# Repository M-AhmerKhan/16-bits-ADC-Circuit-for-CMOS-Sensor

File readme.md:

# Analog-Digital conversion circuit with an interface to a FPGA development board for an X-ray detector module of a 3D breast CT prototype

## Project Overview
This project focuses on the design and development of an ADC electronic circuit for a CMOS sensor coupled with CsI:Tl scintillating crystals to detects X-rays. The circuit samples analog pixels data from the sensor, crucial for analyzing beam geometry and sensor-scintillator response. An FPGA interfaces with the circuit to process the digital data from three sensor channels and store it on a host computer for image processing and analysis.

## Features
- 16-bits ADC circuit for 3 channel CMOS sensor.
- Serial Peripheral Interface (SPI)
- Designed voltage level shifter for interfacing +3.3V Analog front end LM98725 with a +5V CMOS sensor.
- Implemented voltage clamping circuit.
- Interfacing ADC with FPGA (NI sbRIO-9651) via LabVIEW.
- PCB layout and design using EAGLE

## Tools and Technologies

- **EAGLE** for schematic capture and PCB layout
- **LabVIEW** to acquires the digital data from the ADC in a sequence, converts this data into integer values and save the complete pixels data in a text file on the computer from each sensor channel.
- **Arduino** for SPI
- **Oscilloscope** for signal testing.
- **MATLAB** for anylyzing sesor data.

## Circuit Schematic
Here is the circuit schematic designed in EAGLE:

## PCB Layout
The PCB layout was created using EAGLE. Below is a preview of the PCB design:

## Designed PCB
Final designed PCB:

## Interfacing with FPGA

The 16 bits digital data from the ADC is arranged in a particular sequence such that it gives a single pixel value from each three channels of CMOS sensor. Two  LabVIEW programs (VI) source code are written and complied, one on the FPGA also called “target” to collects the sensor digital data and the other on the computer system referred as “host”. This data is received and saved to the host memory in the same order by implementing a FIFO method (First In First Out) that organize and prioritize the data with the time.

Communication and data flow between host computer and FPGA:

## Contact
For any questions, feel free to contact me at: [m.ahmerkhan@outlook.de](mailto:m.ahmerkhan@outlook.de).

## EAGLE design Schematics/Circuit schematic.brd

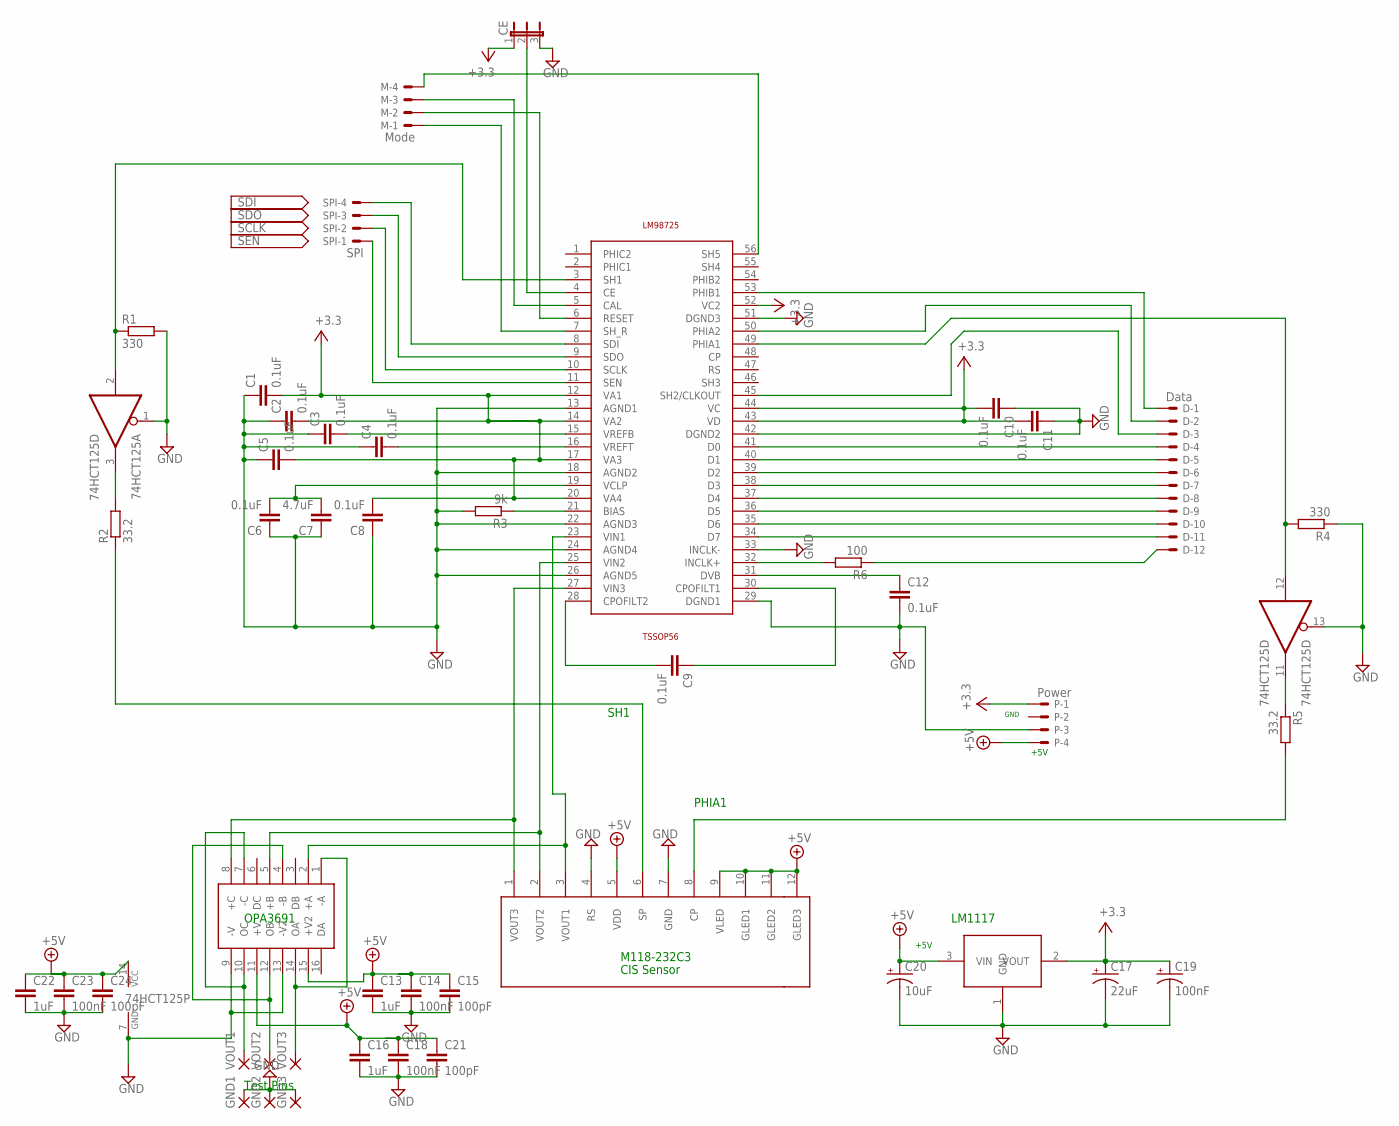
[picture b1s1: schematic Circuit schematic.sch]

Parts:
74HCT125: 74HCT125D; SO14
C1, C2, C3, C4, C5, C6, C8, C9, C10, C11, C12: 0.1uF; C0603
C7: 4.7uF; C0603
C13, C16, C22: 1uF; C0603
C14, C18, C23: 100nF; C0603
C15, C21, C24: 100pF; C0603
C17: 22uF; D/7343-31W
C19: 100nF; A/3216-18W
C20: 10uF; C/6032-28R
CE: JP2E; JP2
D: Data; 53048-12
GND1, GND2, GND3: 3,17/1,3
LM98725: LM98725; TSSOP56
M: Mode; 53048-04
OPA3691: OPA3691; SO16
P: Power; 53048-04
R1, R4: 330; R0603
R2, R5: 33.2; R0603
R3: 9k; R0603
R6: 100; R0603
SENSOR: CIS-M118118; 12PINPAD
SPI: SPI; 53048-04
U$2: LM117; LM
VOUT1, VOUT2, VOUT3: 3,17/1,3

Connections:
+5V: 74HCT125.14 (VCC), C13.1, C14.1, C15.1, C16.1, C18.1, C20.+, C21.1, C22.1, C23.1, C24.1, OPA3691.11 (+V), OPA3691.15 (+V2), P.4, SENSOR.5 (VDD), SENSOR.9 (VLED), SENSOR.10 (GLED1), SENSOR.11 (GLED2), SENSOR.12 (GLED3), U$2.3 (VIN)
GND: 74HCT125.1 (OE), 74HCT125.7 (GND), 74HCT125.13 (OE), C1.1, C2.1, C3.1, C4.1, C5.1, C6.1, C7.1, C8.1, C10.1, C11.1, C12.2, C13.2, C14.2, C15.2, C16.2, C17.-, C18.2, C19.-, C20.-, C21.2, C22.2, C23.2, C24.2, CE.3, GND1.1, GND2.1, GND3.1, LM98725.13 (AGND1), LM98725.18 (AGND2), LM98725.22 (AGND3), LM98725.24 (AGND4), LM98725.26 (AGND5), LM98725.29 (DGND1), LM98725.33 (INCLK-), LM98725.42 (DGND2), LM98725.51 (DGND3), OPA3691.9 (-V), OPA3691.13 (-V2), P.3, R1.2, R3.2, R4.1, SENSOR.4 (RS), SENSOR.7 (GND), U$2.1 (GND)
unnamed: C9.2, LM98725.28 (CPOFILT2)
unnamed: C9.1, LM98725.30 (CPOFILT1)
unnamed: OPA3691.4 (-B), OPA3691.12 (OB), VOUT2.1
unnamed: C12.1, LM98725.31 (DVB)
unnamed: OPA3691.1 (-A), OPA3691.14 (OA), VOUT3.1
unnamed: OPA3691.7 (-C), OPA3691.10 (OC), VOUT1.1
unnamed: LM98725.25 (VIN2), OPA3691.5 (+B), SENSOR.2 (VOUT2)
unnamed: CE.2, LM98725.4 (CE)
unnamed: LM98725.32 (INCLK+), R6.2
unnamed: C4.2, LM98725.16 (VREFT)
unnamed: LM98725.8 (SDI), SPI.4
unnamed: LM98725.21 (BIAS), R3.1
unnamed: C6.2, C7.2, LM98725.19 (VCLP)
unnamed: LM98725.9 (SDO), SPI.3
unnamed: LM98725.10 (SCLK), SPI.2
unnamed: LM98725.5 (CAL), M.3
unnamed: LM98725.11 (SEN), SPI.1
unnamed: LM98725.6 (RESET), M.2
unnamed: LM98725.7 (SH_R), M.1
unnamed: D.12, R6.1
unnamed: D.11, LM98725.34 (D7)
unnamed: D.3, LM98725.45 (SH2/CLKOUT)
unnamed: LM98725.56 (SH5), M.4
unnamed: D.1, LM98725.53 (PHIB1)
unnamed: D.2, LM98725.50 (PHIA2)
unnamed: D.10, LM98725.35 (D6)
unnamed: D.9, LM98725.36 (D5)
unnamed: D.8, LM98725.37 (D4)
unnamed: D.6, LM98725.39 (D2)
unnamed: D.7, LM98725.38 (D3)
unnamed: D.5, LM98725.40 (D1)
unnamed: D.4, LM98725.41 (D0)
unnamed: 74HCT125.3 (O), R2.2
unnamed: R5.2, SENSOR.8 (CP)
unnamed: LM98725.23 (VIN1), OPA3691.2 (+A), SENSOR.3 (VOUT1)
unnamed: R2.1, SENSOR.6 (SP)
unnamed: 74HCT125.2 (I), LM98725.3 (SH1), R1.1
unnamed: C3.2, LM98725.15 (VREFB)
unnamed: 74HCT125.12 (I), LM98725.49 (PHIA1), R4.2
unnamed: 74HCT125.11 (O), R5.1
unnamed: LM98725.27 (VIN3), OPA3691.8 (+C), SENSOR.1 (VOUT3)
V+: C1.2, C2.2, C5.2, C8.2, C10.2, C11.2, C17.+, C19.+, CE.1, LM98725.12 (VA1), LM98725.14 (VA2), LM98725.17 (VA3), LM98725.20 (VA4), LM98725.43 (VD), LM98725.44 (VC), LM98725.52 (VC2), P.1, U$2.2 (VOUT)

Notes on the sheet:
+5V
GND
LM1117
Test Pins
PHIA1
SH1
M118-232C3
CIS Sensor
OPA3691

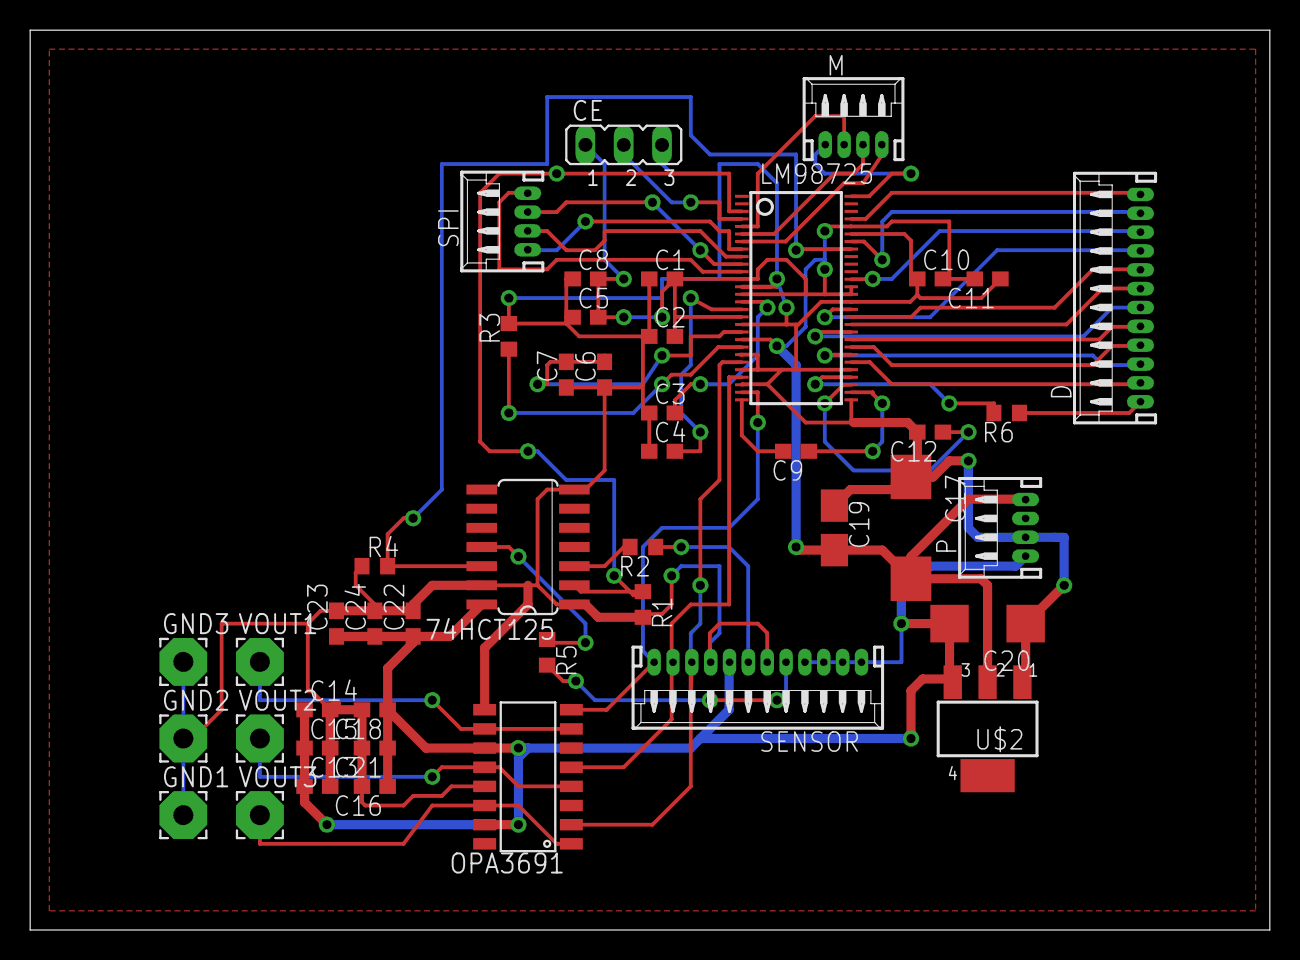
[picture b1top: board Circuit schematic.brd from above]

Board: 2 copper layers, 82.2 x 59.7 mm, 46 parts (0 on the bottom side), 44 nets.

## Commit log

2024-09-21 Rename ADC schematic.png to ADCschematic.png
2024-09-21 Rename PCB Layout (1).png to PCBLayoutGND.png
2024-09-21 Rename PCB Layout (2).png to PCBLayout.png
2024-09-22 Create Schematics
